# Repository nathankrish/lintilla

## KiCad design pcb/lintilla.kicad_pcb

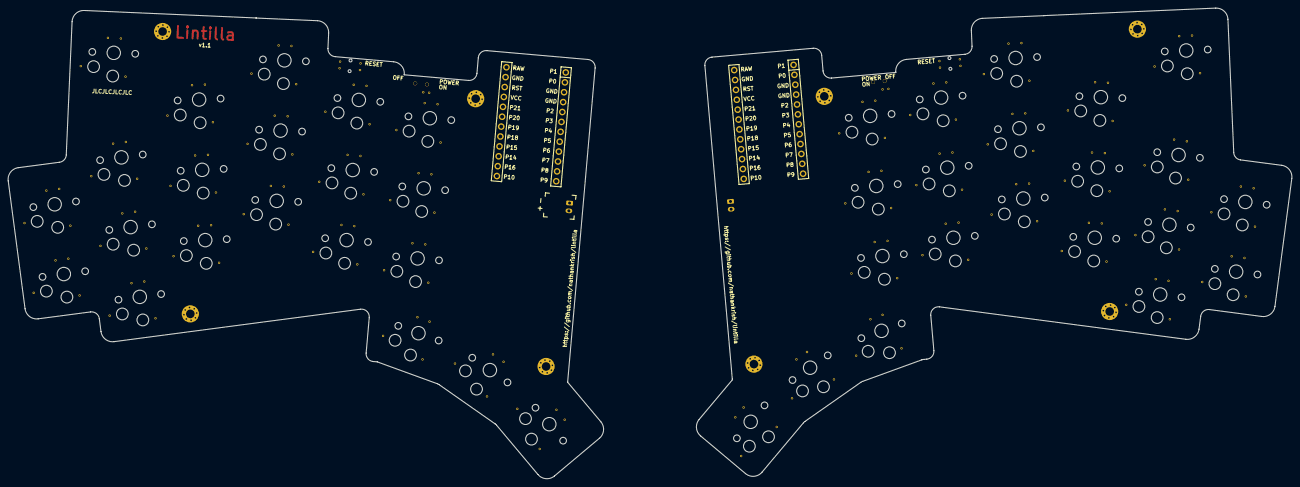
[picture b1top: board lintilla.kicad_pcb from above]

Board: 2 copper layers, 328.4 x 120.4 mm, 92 parts (1 on the bottom side), 65 nets, no tracks yet.

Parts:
B1, B2: Panasonic_EVQPUL_EVQPUC
JST1, JST1#2: battery_connector_jst_ph_2
MCU1, MCU2: mcu_supermini_nrf52840
S1, S2, S3, S4, S5, S6, S7, S8, S9, S10, S11, S12, S13, S14, S15, S16, S17, S18, S19, S20, S21, S22, S23, S24, S25, S26, S27, S28, S29, S30, S31, S32, S33, S34, S35, S36, S37, S38, S39, S40, S41, S42: PG1350
SW1, SW2, SW3, SW4, SW5, SW6, SW7, SW8, SW9, SW10, SW11, SW12, SW13, SW14, SW15, SW16, SW17, SW18, SW19, SW20, SW21, SW22, SW23, SW24, SW25, SW26, SW27, SW28, SW29, SW30, SW31, SW32, SW33, SW34, SW35, SW36, SW37, SW38, SW39, SW40, SW41, SW42: ComboDiode
T1, T2: SPDT_C128955

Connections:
BAT+: T1.1, T2.1
GND: B1.1, B2.1, JST1.1, MCU1.3, MCU1.4, MCU1.23, MCU2.3, MCU2.4, MCU2.23
P0: MCU1.2, MCU2.2
P1: MCU1.1, MCU2.1, SW3.1, SW19.1, SW20.1, SW21.1, SW24.1, SW40.1, SW41.1, SW42.1
P2: MCU1.5, MCU2.5, SW1.1, SW4.1, SW7.1, SW10.1, SW13.1, SW16.1, SW22.1, SW25.1, SW28.1, SW31.1, SW34.1, SW37.1
P3: MCU1.6, MCU2.6, SW2.1, SW5.1, SW8.1, SW11.1, SW14.1, SW17.1, SW23.1, SW26.1, SW29.1, SW32.1, SW35.1, SW38.1
P4: MCU1.7, MCU2.7, S1.1, S2.1, S22.1, S23.1
P5: MCU1.8, MCU2.8, S16.1, S17.1, S18.1, S21.1, S37.1, S38.1, S39.1, S42.1
P6: MCU1.9, MCU2.9, S7.1, S8.1, S9.1, S28.1, S29.1, S30.1
P7: MCU1.10, MCU2.10, S13.1, S14.1, S15.1, S20.1, S34.1, S35.1, S36.1, S41.1
P8: MCU1.11, MCU2.11, S3.1, S4.1, S5.1, S6.1, S24.1, S25.1, S26.1, S27.1
P9: MCU1.12, MCU2.12, S10.1, S11.1, S12.1, S19.1, S31.1, S32.1, S33.1, S40.1
P10: MCU1.13, MCU2.13, SW6.1, SW9.1, SW12.1, SW15.1, SW18.1, SW27.1, SW30.1, SW33.1, SW36.1, SW39.1
P14: MCU1.15, MCU2.15
P15: MCU1.16, MCU2.16
P16: MCU1.14, MCU2.14
P18: MCU1.17, MCU2.17
P19: MCU1.18, MCU2.18
P20: MCU1.19, MCU2.19
P21: MCU1.20, MCU2.20
RAW: MCU1.24, MCU2.24, T1.2, T1.3, T2.2, T2.3
RST: B1.2, B2.2, MCU1.22, MCU2.22
VCC: MCU1.21, MCU2.21
index_bottom: S13.2, SW13.2
index_home: S14.2, SW14.2
index_top: S15.2, SW15.2
inner_bottom: S16.2, SW16.2
inner_home: S17.2, SW17.2
inner_top: S18.2, SW18.2
middle_bottom: S10.2, SW10.2
middle_home: S11.2, SW11.2
middle_top: S12.2, SW12.2
mirror_index_bottom: S34.2, SW34.2
mirror_index_home: S35.2, SW35.2
mirror_index_top: S36.2, SW36.2
mirror_inner_bottom: S37.2, SW37.2
mirror_inner_home: S38.2, SW38.2
mirror_inner_top: S39.2, SW39.2
mirror_middle_bottom: S31.2, SW31.2
mirror_middle_home: S32.2, SW32.2
mirror_middle_top: S33.2, SW33.2
mirror_outer_bottom: S22.2, SW22.2
mirror_outer_home: S23.2, SW23.2
mirror_pinky_bottom: S24.2, SW24.2
mirror_pinky_fn: S27.2, SW27.2
mirror_pinky_home: S25.2, SW25.2
mirror_pinky_top: S26.2, SW26.2
mirror_primary_spot: S41.2, SW41.2
mirror_reachy_spot: S42.2, SW42.2
mirror_ring_bottom: S28.2, SW28.2
mirror_ring_home: S29.2, SW29.2
mirror_ring_top: S30.2, SW30.2
mirror_secondary_spot: S40.2, SW40.2
outer_bottom: S1.2, SW1.2
outer_home: S2.2, SW2.2
pinky_bottom: S3.2, SW3.2
pinky_fn: S6.2, SW6.2
pinky_home: S4.2, SW4.2
pinky_top: S5.2, SW5.2
primary_spot: S20.2, SW20.2
reachy_spot: S21.2, SW21.2
ring_bottom: S7.2, SW7.2
ring_home: S8.2, SW8.2
ring_top: S9.2, SW9.2
secondary_spot: S19.2, SW19.2

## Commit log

2025-06-28 Change to supermini, add power jack, mirror design
